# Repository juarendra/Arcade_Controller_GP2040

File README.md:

# Arcade_Controller_GP2040
Hardware and Firmware of Arcade Controller Based RP2040 as Microcontroller and GP2040 as Frimware

# Spesification
- Input Power VIA USB 5VDC
- GP2040 Controller Firmware
- Plugable Terminal Block and molex JST-XH for Port To External Item
- Pin Header 2x10 2.54 for Port To External Item
- LED RGB on BOARD
- Support RP2040 Raspberry Pi PICO or Weact RP2040
- I2C Port 
- LED Player Port with Resistor On board 330OHM
- 3v3 and GND port Molex for external perpose

# Privew Hardware 

# Pinout
## Pinout RP2040

# Documentation 
- [Dimension](https://github.com/juarendra/Arcade_Controller_GP2040/blob/main/3D/Dimension_arcadeController.pdf)
- [BOM](https://github.com/juarendra/Arcade_Controller_GP2040/blob/main/DOC/bom.csv)
- [Pinout RP2040](https://github.com/juarendra/Arcade_Controller_GP2040/blob/main/DOC/Arcade_Controller_GP2040_Pinout.pdf)

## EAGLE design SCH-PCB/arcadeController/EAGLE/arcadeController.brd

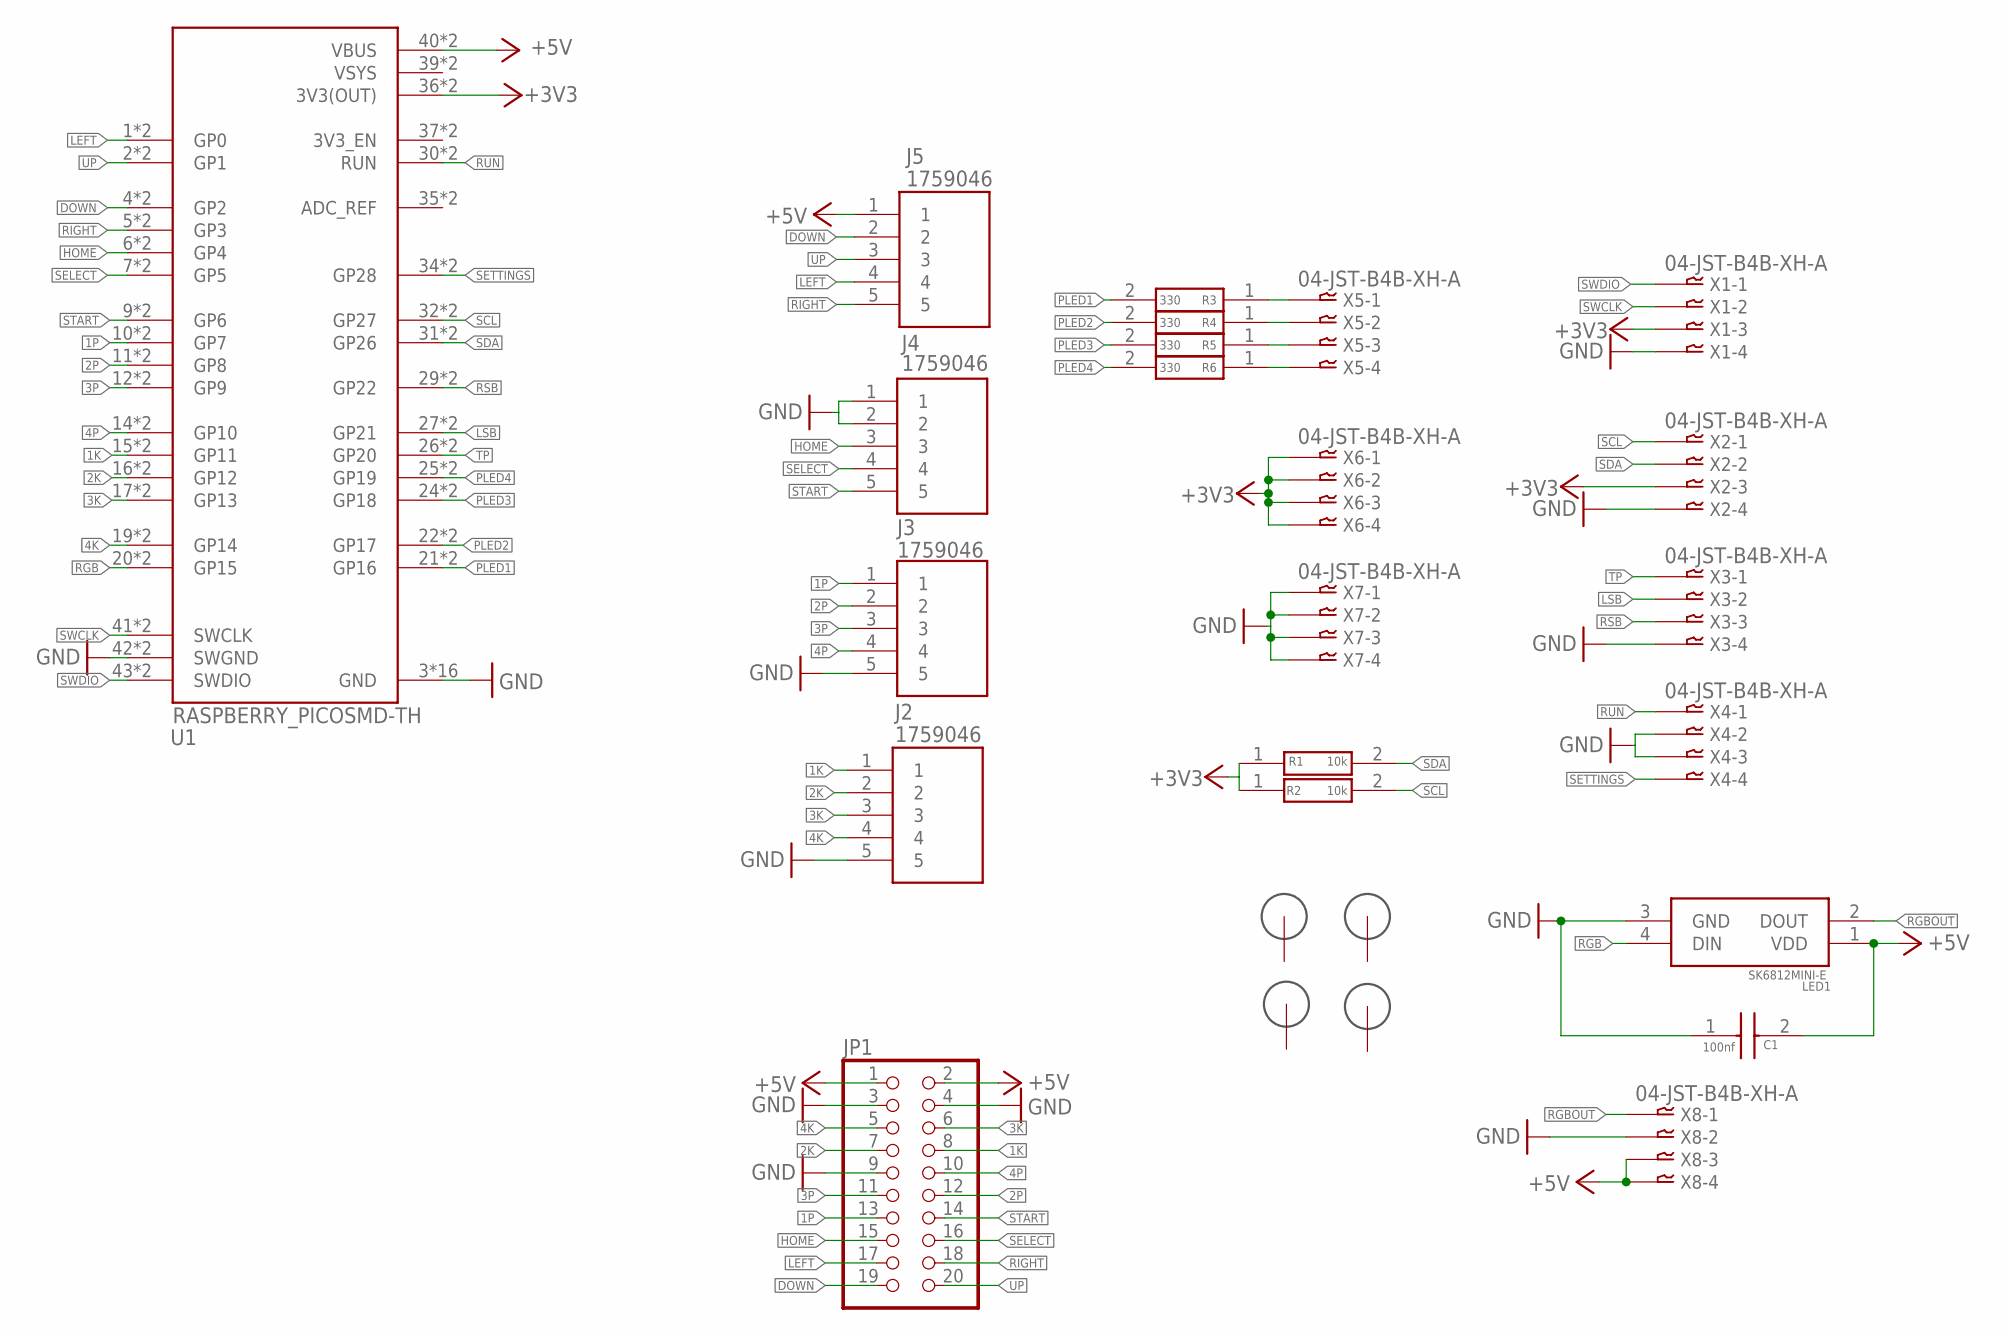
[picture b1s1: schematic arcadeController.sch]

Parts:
C1: 100nf; CAPC2012X94N
H1, H2, H3, H4: 3MM_HOLE
J2, J3, J4, J5: 1759046; SHDRRA5W103P0X508_1X5_2540X120
JP1: PINHD-2X10; 2X10
LED1: SK6812MINI-E; SK6812MINIE
R1, R2: 10k; RESC2012X60N
R3, R4, R5, R6: 330; RESC1608X55N
U1: RASPBERRY_PICOSMD-TH; PICO-PKG
X1, X2, X3, X4, X5, X6, X7, X8: 04-JST-B4B-XH-A; B4B-XH

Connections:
1K: J2.1, JP1.8, U1.15 (GP11), U1.P$15 (GP11)
1P: J3.1, JP1.13, U1.10 (GP7), U1.P$10 (GP7)
2K: J2.2, JP1.7, U1.16 (GP12), U1.P$16 (GP12)
2P: J3.2, JP1.12, U1.11 (GP8), U1.P$11 (GP8)
3K: J2.3, JP1.6, U1.17 (GP13), U1.P$17 (GP13)
3P: J3.3, JP1.11, U1.12 (GP9), U1.P$12 (GP9)
4K: J2.4, JP1.5, U1.19 (GP14), U1.P$19 (GP14)
4P: J3.4, JP1.10, U1.14 (GP10), U1.P$14 (GP10)
+3V3: R1.1, R2.1, U1.36 (3V3(OUT)), U1.P$36 (3V3(OUT)), X1.P$3, X2.P$3, X6.P$1, X6.P$2, X6.P$3, X6.P$4
+5V: C1.2, J5.1, JP1.1, JP1.2, LED1.1 (VDD), U1.40 (VBUS), U1.P$40 (VBUS), X8.P$3, X8.P$4
DOWN: J5.2, JP1.19, U1.4 (GP2), U1.P$4 (GP2)
GND: C1.1, J2.5, J3.5, J4.1, J4.2, JP1.3, JP1.4, JP1.9, LED1.3 (GND), U1.3 (GND), U1.8 (GND), U1.13 (GND), U1.18 (GND), U1.23 (GND), U1.28 (GND), U1.33 (GND), U1.38 (GND), U1.42 (SWGND), U1.P$3 (GND), U1.P$8 (GND), U1.P$13 (GND), U1.P$18 (GND), U1.P$23 (GND), U1.P$28 (GND), U1.P$33 (GND), U1.P$38 (GND), U1.P$42 (SWGND), X1.P$4, X2.P$4, X3.P$4, X4.P$2, X4.P$3, X7.P$1, X7.P$2, X7.P$3, X7.P$4, X8.P$2
HOME: J4.3, JP1.15, U1.6 (GP4), U1.P$6 (GP4)
LEFT: J5.4, JP1.17, U1.1 (GP0), U1.P$1 (GP0)
LSB: U1.27 (GP21), U1.P$27 (GP21), X3.P$2
unnamed: R3.1, X5.P$1
unnamed: R4.1, X5.P$2
unnamed: R5.1, X5.P$3
unnamed: R6.1, X5.P$4
PLED1: R3.2, U1.21 (GP16), U1.P$21 (GP16)
PLED2: R4.2, U1.22 (GP17), U1.P$22 (GP17)
PLED3: R5.2, U1.24 (GP18), U1.P$24 (GP18)
PLED4: R6.2, U1.25 (GP19), U1.P$25 (GP19)
RGB: LED1.4 (DIN), U1.20 (GP15), U1.P$20 (GP15)
RGBOUT: LED1.2 (DOUT), X8.P$1
RIGHT: J5.5, JP1.18, U1.5 (GP3), U1.P$5 (GP3)
RSB: U1.29 (GP22), U1.P$29 (GP22), X3.P$3
RUN: U1.30 (RUN), U1.P$30 (RUN), X4.P$1
SCL: R2.2, U1.32 (GP27), U1.P$32 (GP27), X2.P$1
SDA: R1.2, U1.31 (GP26), U1.P$31 (GP26), X2.P$2
SELECT: J4.4, JP1.16, U1.7 (GP5), U1.P$7 (GP5)
SETTINGS: U1.34 (GP28), U1.P$34 (GP28), X4.P$4
START: J4.5, JP1.14, U1.9 (GP6), U1.P$9 (GP6)
SWCLK: U1.41 (SWCLK), U1.P$41 (SWCLK), X1.P$2
SWDIO: U1.43 (SWDIO), U1.P$43 (SWDIO), X1.P$1
TP: U1.26 (GP20), U1.P$26 (GP20), X3.P$1
UP: J5.3, JP1.20, U1.2 (GP1), U1.P$2 (GP1)
VSYS: U1.39 (VSYS), U1.P$39 (VSYS)

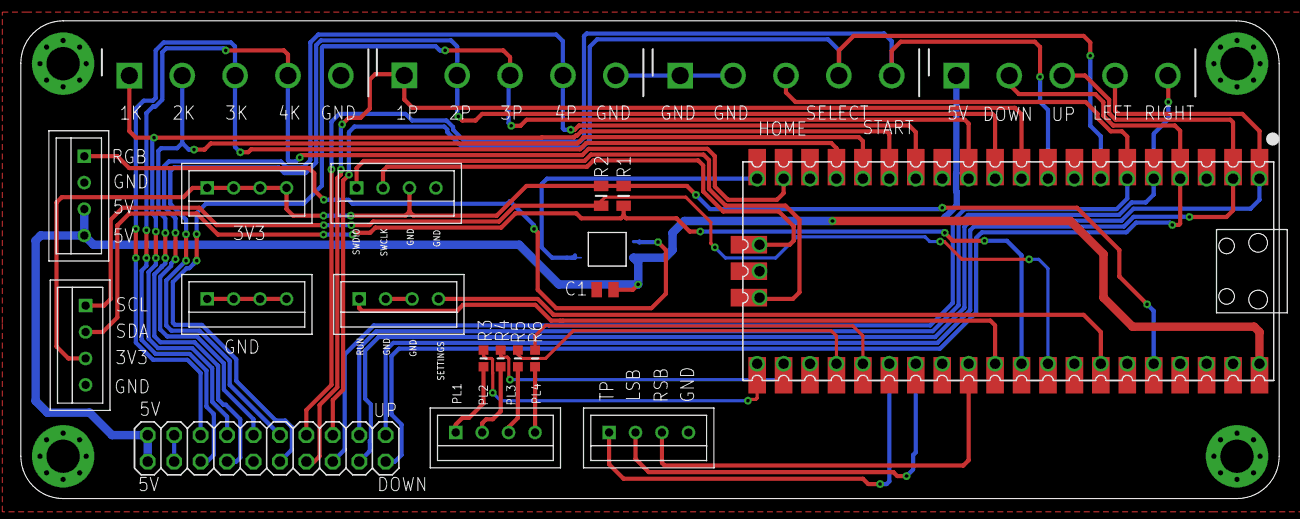
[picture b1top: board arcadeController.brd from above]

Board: 2 copper layers, 120.8 x 45.8 mm, 26 parts (1 on the bottom side), 38 nets.

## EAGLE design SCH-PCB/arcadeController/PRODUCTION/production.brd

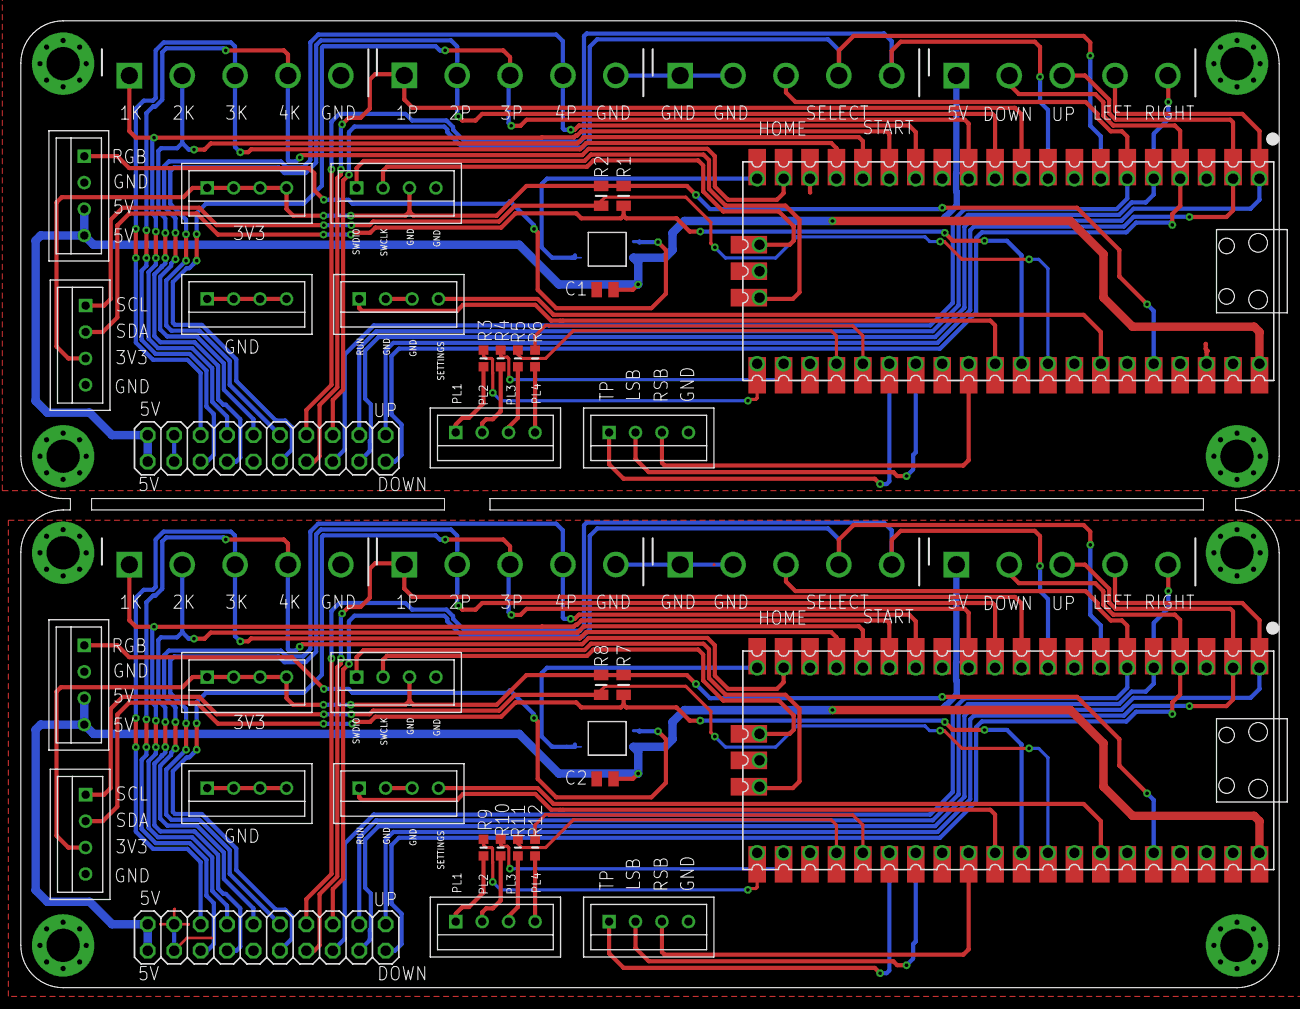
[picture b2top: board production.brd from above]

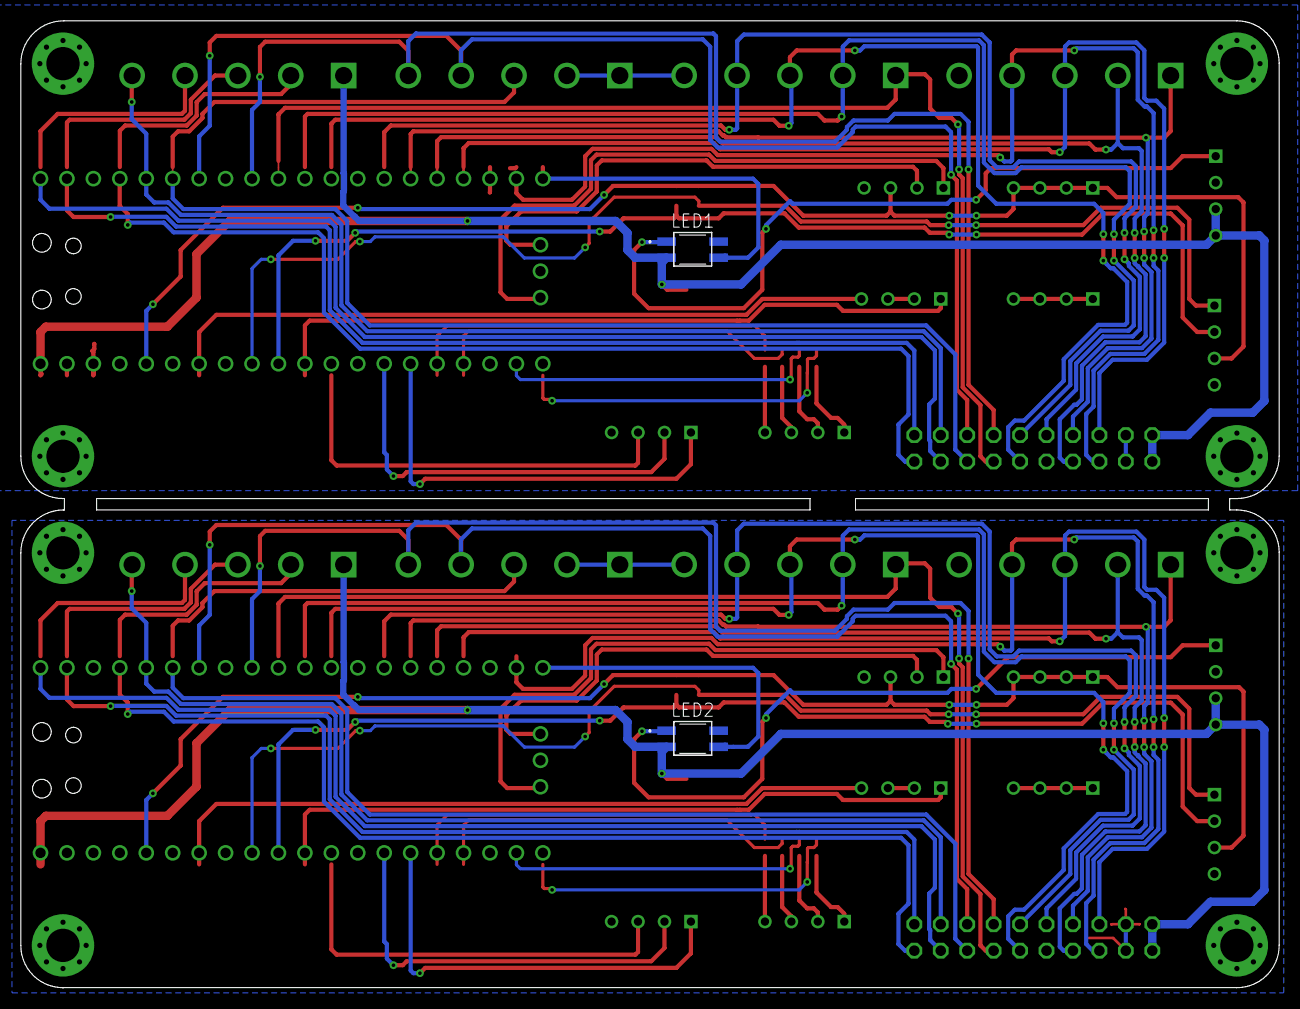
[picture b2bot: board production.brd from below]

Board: 2 copper layers, 120.8 x 92.8 mm, 52 parts (2 on the bottom side), 76 nets.

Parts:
C1, C2: 100nf; CAPC2012X94N
H1, H2, H3, H4, H5, H6, H7, H8: 3MM_HOLE
J1, J2, J3, J4, J5, J6, J7, J8: 1759046; SHDRRA5W103P0X508_1X5_2540X120
JP1, JP2: 2X10
LED1, LED2: SK6812MINI-E; SK6812MINIE
R1, R2, R7, R8: 10k; RESC2012X60N
R3, R4, R5, R6, R9, R10, R11, R12: 330; RESC1608X55N
U1, U2: RASPBERRY_PICOSMD-TH; PICO-PKG
X1, X2, X3, X4, X5, X6, X7, X8, X9, X10, X11, X12, X13, X14, X15, X16: 04-JST-B4B-XH-A; B4B-XH

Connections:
1K: J2.1, JP1.8, U1.15, U1.P$15
1K1: J1.1, JP2.8, U2.15, U2.P$15
1P: J3.1, JP1.13, U1.10, U1.P$10
1P1: J6.1, JP2.13, U2.10, U2.P$10
2K: J2.2, JP1.7, U1.16, U1.P$16
2K1: J1.2, JP2.7, U2.16, U2.P$16
2P: J3.2, JP1.12, U1.11, U1.P$11
2P1: J6.2, JP2.12, U2.11, U2.P$11
3K: J2.3, JP1.6, U1.17, U1.P$17
3K1: J1.3, JP2.6, U2.17, U2.P$17
3P: J3.3, JP1.11, U1.12, U1.P$12
3P1: J6.3, JP2.11, U2.12, U2.P$12
4K: J2.4, JP1.5, U1.19, U1.P$19
4K1: J1.4, JP2.5, U2.19, U2.P$19
4P: J3.4, JP1.10, U1.14, U1.P$14
4P1: J6.4, JP2.10, U2.14, U2.P$14
+3V1: R7.1, R8.1, U2.36, U2.P$36, X9.P$3, X10.P$3, X14.P$1, X14.P$2, X14.P$3, X14.P$4
+3V3: R1.1, R2.1, U1.36, U1.P$36, X1.P$3, X2.P$3, X6.P$1, X6.P$2, X6.P$3, X6.P$4
+5V: C1.2, J5.1, JP1.1, JP1.2, LED1.1, U1.40, U1.P$40, X8.P$3, X8.P$4
+5V1: C2.2, J8.1, JP2.1, JP2.2, LED2.1, U2.40, U2.P$40, X16.P$3, X16.P$4
DOWN: J5.2, JP1.19, U1.4, U1.P$4
DOWN1: J8.2, JP2.19, U2.4, U2.P$4
GND: C1.1, J2.5, J3.5, J4.1, J4.2, JP1.3, JP1.4, JP1.9, LED1.3, U1.3, U1.8, U1.13, U1.18, U1.23, U1.28, U1.33, U1.38, U1.42, U1.P$3, U1.P$8, U1.P$13, U1.P$18, U1.P$23, U1.P$28, U1.P$33, U1.P$38, U1.P$42, X1.P$4, X2.P$4, X3.P$4, X4.P$2, X4.P$3, X7.P$1, X7.P$2, X7.P$3, X7.P$4, X8.P$2
GND1: C2.1, J1.5, J6.5, J7.1, J7.2, JP2.3, JP2.4, JP2.9, LED2.3, U2.3, U2.8, U2.13, U2.18, U2.23, U2.28, U2.33, U2.38, U2.42, U2.P$3, U2.P$8, U2.P$13, U2.P$18, U2.P$23, U2.P$28, U2.P$33, U2.P$38, U2.P$42, X9.P$4, X10.P$4, X11.P$4, X12.P$2, X12.P$3, X15.P$1, X15.P$2, X15.P$3, X15.P$4, X16.P$2
HOME: J4.3, JP1.15, U1.6, U1.P$6
HOME1: J7.3, JP2.15, U2.6, U2.P$6
LEFT: J5.4, JP1.17, U1.1, U1.P$1
LEFT1: J8.4, JP2.17, U2.1, U2.P$1
LSB: U1.27, U1.P$27, X3.P$2
LSB1: U2.27, U2.P$27, X11.P$2
unnamed: R9.1, X13.P$1
unnamed: R10.1, X13.P$2
unnamed: R11.1, X13.P$3
unnamed: R12.1, X13.P$4
unnamed: R3.1, X5.P$1
unnamed: R4.1, X5.P$2
unnamed: R5.1, X5.P$3
unnamed: R6.1, X5.P$4
PLED1: R3.2, U1.21, U1.P$21
PLED2: R4.2, U1.22, U1.P$22
PLED3: R5.2, U1.24, U1.P$24
PLED4: R6.2, U1.25, U1.P$25
PLED5: R9.2, U2.21, U2.P$21
PLED6: R10.2, U2.22, U2.P$22
PLED7: R11.2, U2.24, U2.P$24
PLED8: R12.2, U2.25, U2.P$25
RGB: LED1.4, U1.20, U1.P$20
RGB1: LED2.4, U2.20, U2.P$20
RGBOUT: LED1.2, X8.P$1
RGBOUT1: LED2.2, X16.P$1
RIGHT: J5.5, JP1.18, U1.5, U1.P$5
RIGHT1: J8.5, JP2.18, U2.5, U2.P$5
RSB: U1.29, U1.P$29, X3.P$3
RSB1: U2.29, U2.P$29, X11.P$3
RUN: U1.30, U1.P$30, X4.P$1
RUN1: U2.30, U2.P$30, X12.P$1
SCL: R2.2, U1.32, U1.P$32, X2.P$1
SCL1: R8.2, U2.32, U2.P$32, X10.P$1
SDA: R1.2, U1.31, U1.P$31, X2.P$2
SDA1: R7.2, U2.31, U2.P$31, X10.P$2
SELECT: J4.4, JP1.16, U1.7, U1.P$7
SELECT1: J7.4, JP2.16, U2.7, U2.P$7
SETTINGS: U1.34, U1.P$34, X4.P$4
SETTINGS1: U2.34, U2.P$34, X12.P$4
START: J4.5, JP1.14, U1.9, U1.P$9
START1: J7.5, JP2.14, U2.9, U2.P$9
SWCLK: U1.41, U1.P$41, X1.P$2
SWCLK1: U2.41, U2.P$41, X9.P$2
SWDIO: U1.43, U1.P$43, X1.P$1
SWDIO1: U2.43, U2.P$43, X9.P$1
TP: U1.26, U1.P$26, X3.P$1
TP1: U2.26, U2.P$26, X11.P$1
UP: J5.3, JP1.20, U1.2, U1.P$2
UP1: J8.3, JP2.20, U2.2, U2.P$2
VSYS: U1.39, U1.P$39
VSYS1: U2.39, U2.P$39

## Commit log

2024-05-16 FEAT: add 3D model
2024-05-16 FEAT: edit document
2024-05-16 FEAT: add BOM
2024-06-03 FIX: PCB design there are line with <0.1mm
2024-06-25 FEAT: add pinout rp2040
2024-06-25 FEAT: update readme
2024-07-10 DOC: add documentation and image
2024-07-10 DOC: update readme
2024-07-10 FEAT: update image
